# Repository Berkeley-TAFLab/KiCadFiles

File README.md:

# KiCadFiles
Attempting version control on KiCadFiles. Hopefully this works.

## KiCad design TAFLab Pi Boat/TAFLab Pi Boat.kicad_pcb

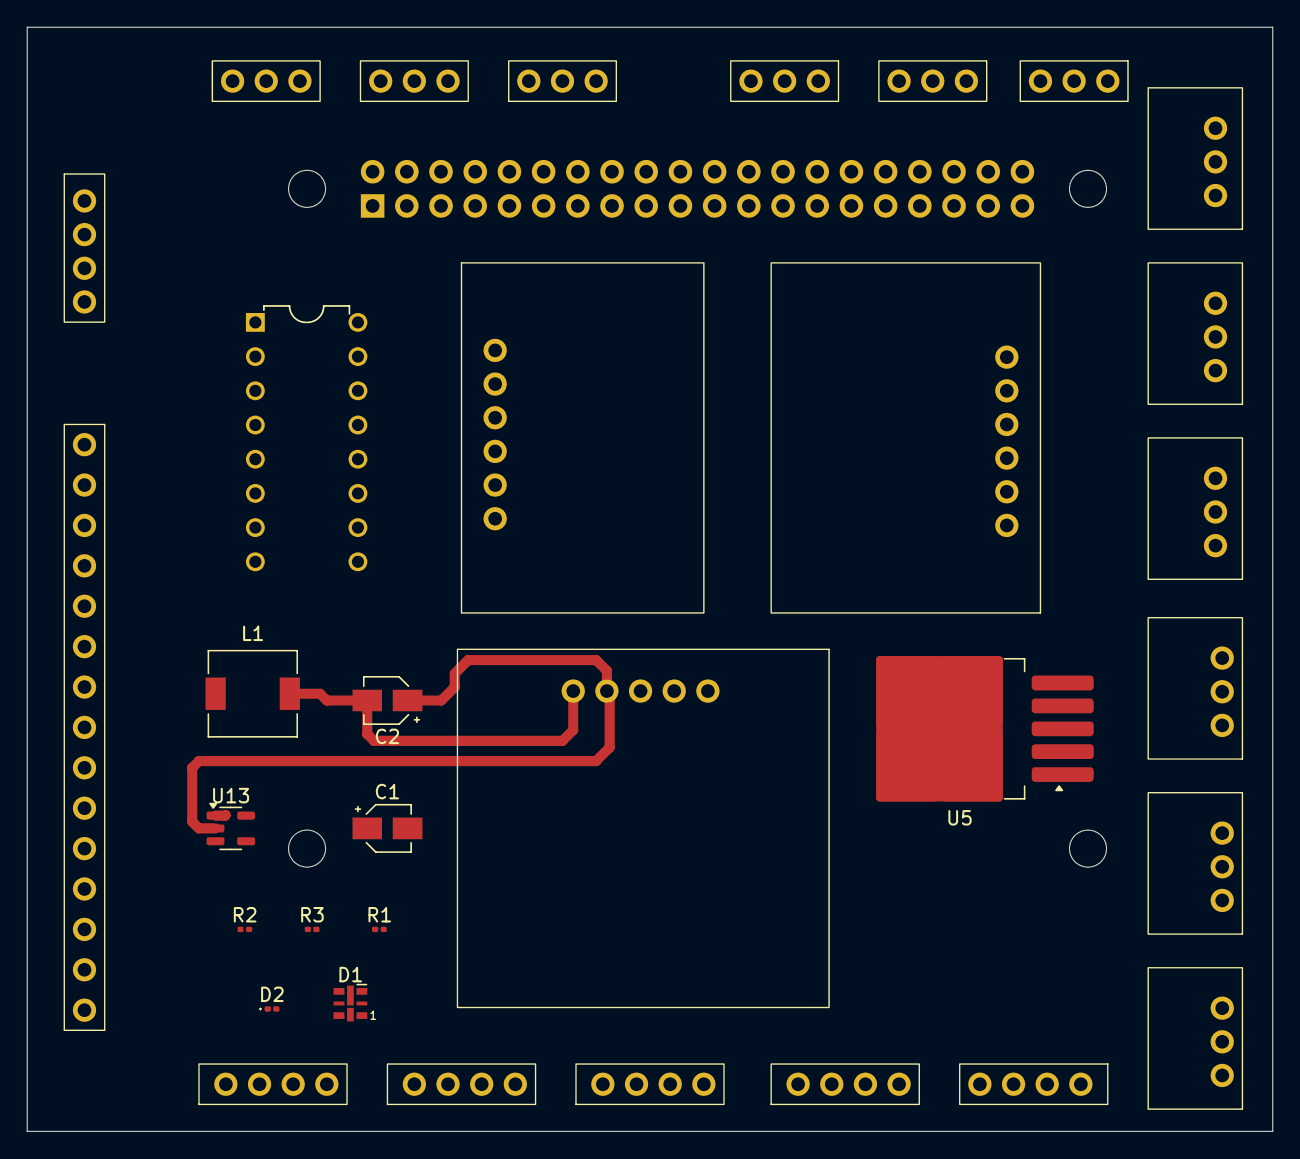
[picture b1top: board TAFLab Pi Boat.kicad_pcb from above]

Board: 2 copper layers, 92.5 x 82.0 mm, 34 parts (0 on the bottom side), 33 nets.

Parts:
C1: 680 uF; CP_Elec_3x5.3
C2: 220 uF; CP_Elec_3x5.3
D1: LED; LED-APA102-2020
D2: D; D_0201_0603Metric
L1: 33uH; L_6.3x6.3_H3
R1: 300Ω; R_0201_0603Metric
R2: 160Ω; R_0201_0603Metric
R3: 10Ω; R_0201_0603Metric
RP1: Raspberry_Pi_2_3; RaspberryPi_4
U4: GT-U7_GPS
U5: LM2596S-5; TO-263-5_TabPin3
U6: MPU6050_IMU_Accelerometer
U7, U8, U9: DS18B20_Water_Temp_Sensor
U10, U11, U12: HW038_WaterLevelSensor
U13: AD8603; TSOT-23-5
U14, U25, U26, U27, U28, U29: Default4Pin
U15: INA219_BatteryPowerSensor
U19, U20, U21, U22, U23, U24: Default3Pin
U33: MCP3008
U34: RearWireConnector

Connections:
+3.3V: RP1.1 (+3.3V_1), U33.15 (Vref), U33.16 (Vdd)
+5V: C2.2, L1.2, R1.1, RP1.2 (+5V_1), U4.5 (5V), U5.4 (FB), U6.1 (5V), U7.2 (5V), U8.2 (5V), U9.2 (5V), U10.2 (5V), U11.2 (5V), U12.2 (5V), U13.3 (+), U14.1 (5V), U15.1 (5V), U19.1 (5V), U20.1 (5V), U21.1 (5V), U22.1 (5V), U23.1 (5V), U24.1 (5V), U25.1 (5V), U26.1 (5V), U27.1 (5V), U28.1 (5V), U29.1 (5V), U34.1 (5V), U34.4 (5V)
+8V: R2.2, U13.1, U34.7 (8V), U34.12 (8V)
A0: U33.1 (CH0), U34.14 (ANA)
A1: U10.1 (ANA), U33.2 (CH1)
A2: U11.1 (ANA), U33.3 (CH2)
A3: U12.1 (ANA), U33.4 (CH3)
A4: U22.3 (DIG/ANA), U33.5 (CH4)
A5: U23.3 (DIG/ANA), U33.6 (CH5)
A6: U24.3 (DIG/ANA), U33.7 (CH6)
BAT+: C1.2, U5.1 (VIN), U34.10 (BAT+)
BAT-: C1.1, U5.5 (~ON/OFF), U34.11 (BAT-)
CLK: RP1.40 (GPIO21/SPI0_SCLK1), U33.13 (CLK)
CS/SHDN: RP1.11 (GPIO_17/SPI1_CS1), U33.10 (~CS/SHDN)
D0: RP1.7 (GPIO_4/GPCLK0), U7.1 (DIG)
D1: RP1.13 (GPIO27), U8.1 (DIG)
D2: RP1.15 (GPIO_22), U9.1 (DIG)
D3: RP1.16 (GPIO_23), U19.3 (DIG/ANA)
D4: RP1.19 (GPIO_10/SPI0_MOSI), U20.3 (DIG/ANA)
D5: RP1.22 (GPIO_25), U21.3 (DIG/ANA)
DIN: RP1.38 (GPIO20/SPI0_MOSI1), U33.11 (Din)
DOUT: RP1.35 (GPIO19/SPI0_MISO1/PWM1), U33.12 (Dout)
GND: C2.1, D1.1 (K), D2.2 (A), R3.2, RP1.6 (GND_1), U4.4 (GND), U5.3 (GND), U6.3 (GND), U7.3 (GND), U8.3 (GND), U9.3 (GND), U10.3 (GND), U11.3 (GND), U12.3 (GND), U13.2 (V-), U14.2 (GND), U15.2 (GND), U19.2 (GND), U20.2 (GND), U21.2 (GND), U22.2 (GND), U23.2 (GND), U24.2 (GND), U25.2 (GND), U26.2 (GND), U27.2 (GND), U28.2 (GND), U29.2 (GND), U33.9 (DGND), U33.14 (AGND), U34.2 (GND), U34.5 (GND), U34.8 (GND), U34.13 (GND)
unnamed: D1.2 (A), R1.2
unnamed: D2.1 (K), L1.1, U5.2 (OUT)
unnamed: R2.1, R3.1, U13.4 (-)
PWM0: RP1.32 (GPIO12/PWM0), U34.9 (DIG)
PWM1: RP1.33 (GPIO13/PWM1), U34.6 (DIG)
PWM2: RP1.12 (GPIO_18/PWM0/SPI1_CS0), U34.3 (DIG)
RX0: RP1.8 (GPIO_14/[UART]_TXD0), U4.3 (RX)
SCL: RP1.5 (GPIO_3/[I2C]_SCL), U6.4 (SCL), U14.4 (SCL), U15.3 (SCL), U25.4 (SCL), U26.4 (SCL), U27.4 (SCL), U28.4 (SCL), U29.4 (SCL)
SDA: RP1.3 (GPIO_2/[I2C]_SDA), U6.5 (SDA), U14.3 (SDA), U15.4 (SDA), U25.3 (SDA), U26.3 (SDA), U27.3 (SDA), U28.3 (SDA), U29.3 (SDA)
TX0: RP1.10 (GPIO_15/[UART]_RXD0), U4.2 (TX)

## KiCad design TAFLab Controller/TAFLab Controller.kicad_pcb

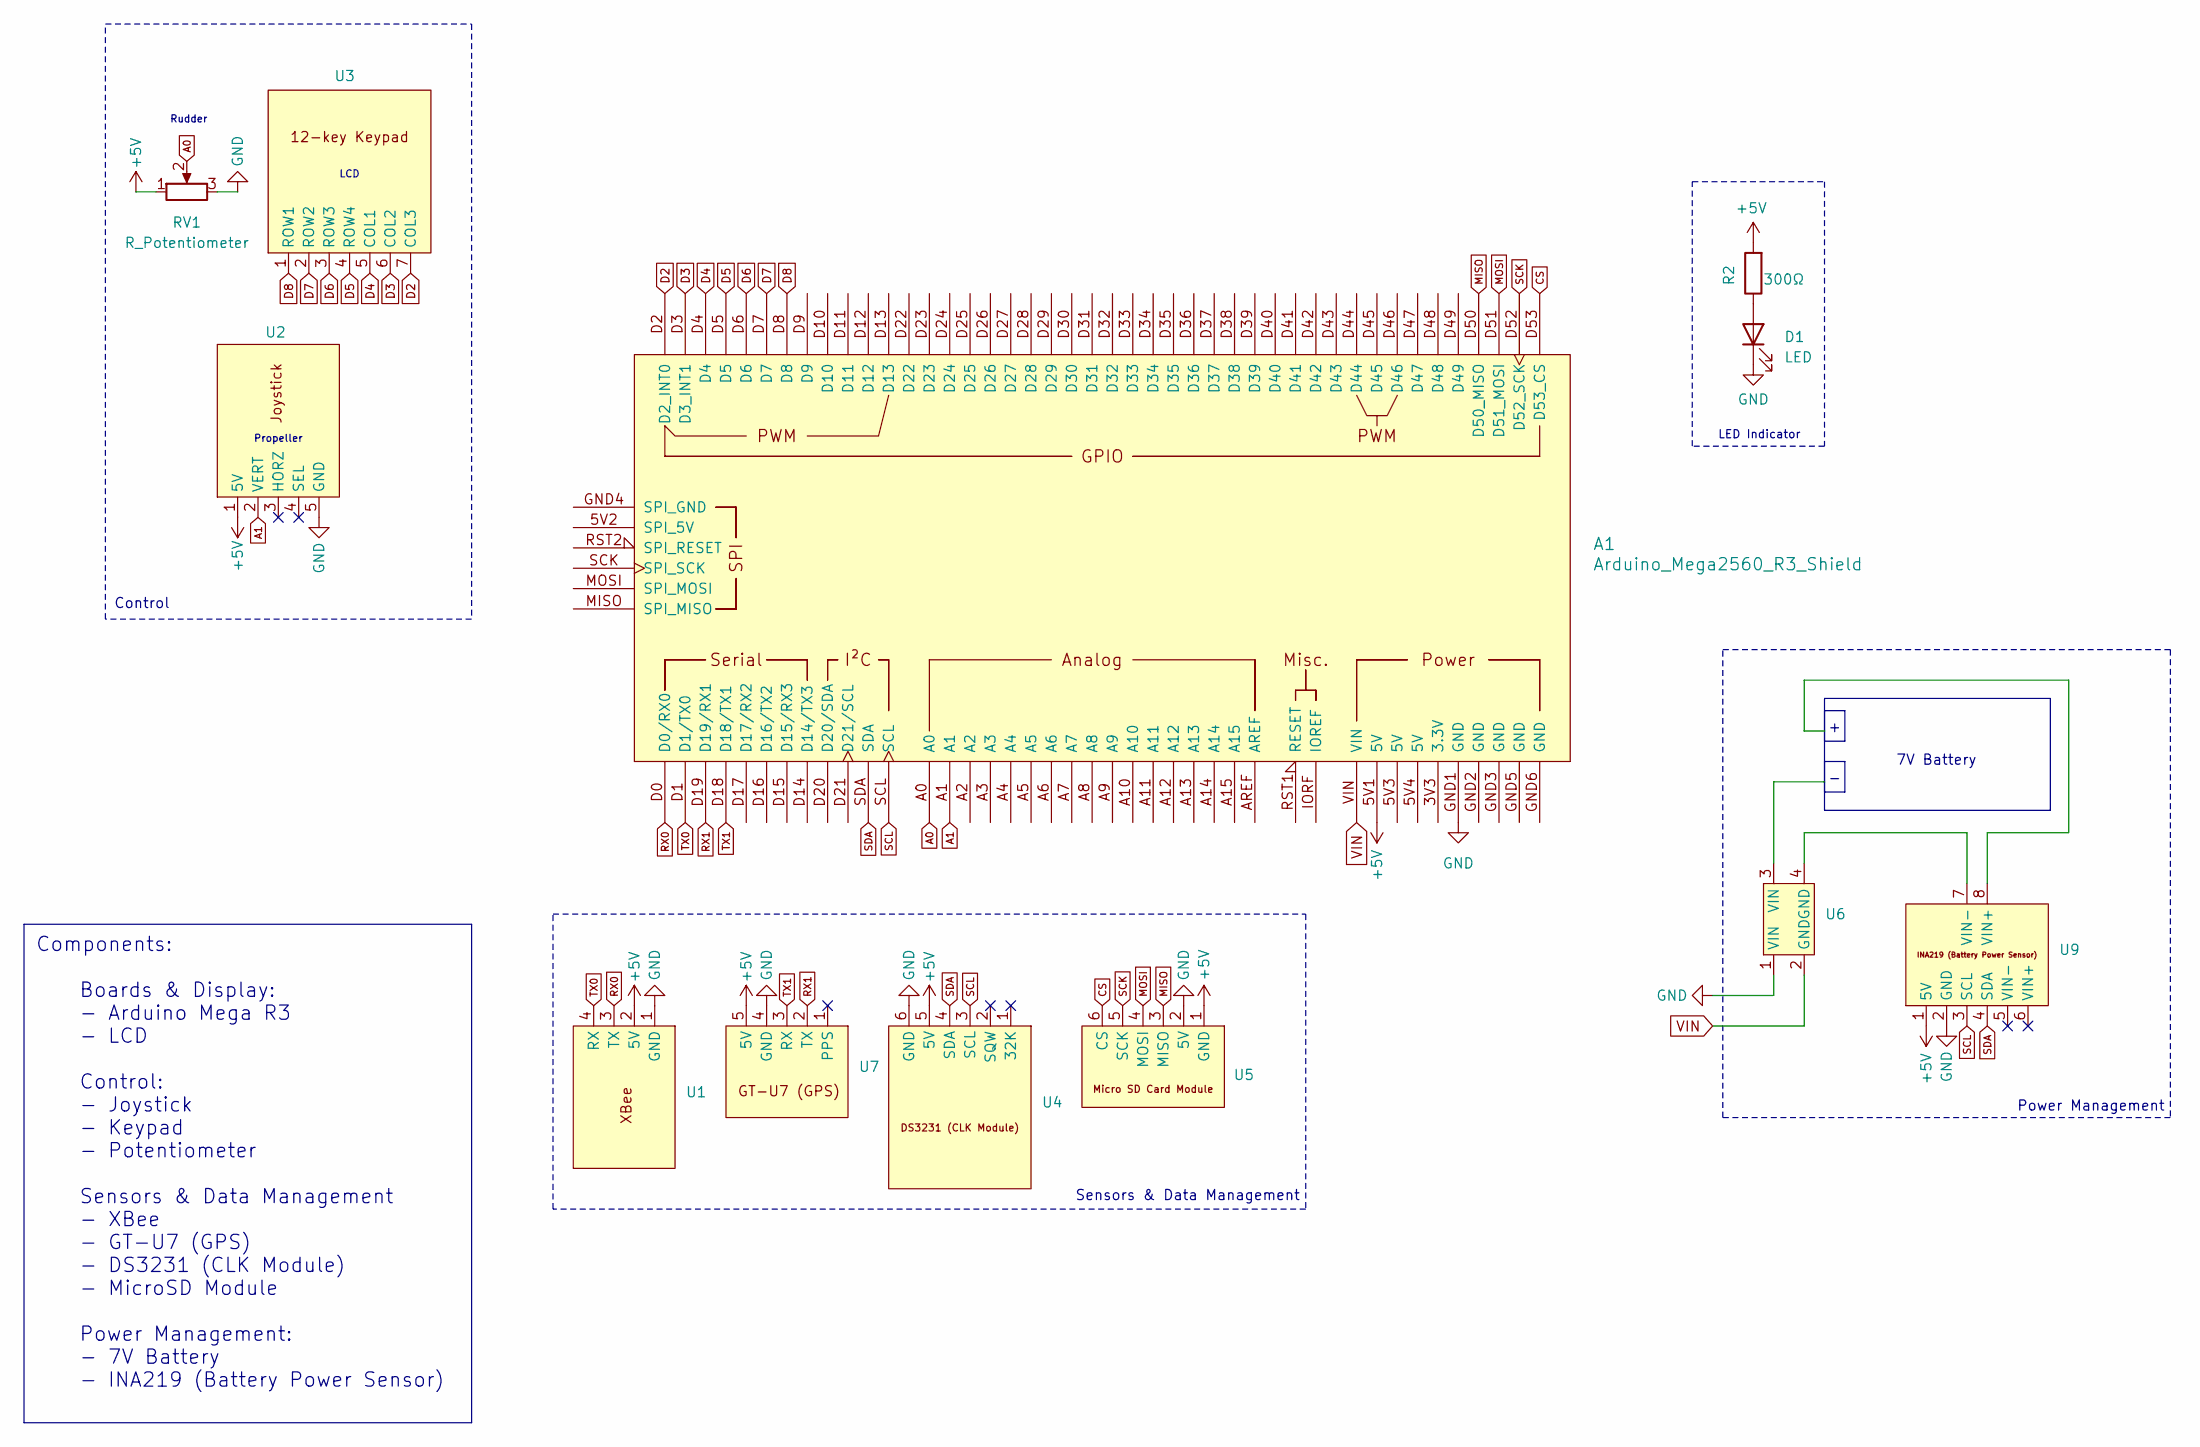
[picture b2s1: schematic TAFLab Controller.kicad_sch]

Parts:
A1: Arduino_Mega2560_R3_Shield
D1: LED; Default2Pin
R2: 300Ω; Default2Pin
RV1: R_Potentiometer; Potentiometer
U1: XBeeBreakout
U2: JoyStick
U3: Keypad
U4: HW84_DS3231_CLK_Module
U5: Micro_SD_Module
U6: VinArduinoConnector
U7: GT-U7_GPS
U9: INA219_BatteryPowerSensor

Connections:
+5V: A1.5V1 (5V), R2.2, RV1.1, U1.2 (5V), U2.1 (5V), U4.5 (5V), U5.1 (GND), U7.5 (5V), U9.1 (5V)
A0: A1.A0, RV1.2
A1: A1.A1, U2.2 (VERT)
CS: A1.D53 (D53_CS), U5.6 (CS)
D2: A1.D2 (D2_INT0), U3.7 (COL3)
D3: A1.D3 (D3_INT1), U3.6 (COL2)
D4: A1.D4, U3.5 (COL1)
D5: A1.D5, U3.4 (ROW4)
D6: A1.D6, U3.3 (ROW3)
D7: A1.D7, U3.2 (ROW2)
D8: A1.D8, U3.1 (ROW1)
GND: A1.GND1 (GND), D1.1 (K), RV1.3, U1.1 (GND), U2.5 (GND), U4.6 (GND), U5.2 (5V), U6.1 (VIN), U7.4 (GND), U9.2 (GND)
MISO: A1.D50 (D50_MISO), U5.3 (MISO)
MOSI: A1.D51 (D51_MOSI), U5.4 (MOSI)
unnamed: D1.2 (A), R2.1
RX0: A1.D0 (D0/RX0), U1.3 (TX)
RX1: A1.D19 (D19/RX1), U7.2 (TX)
SCK: A1.D52 (D52_SCK), U5.5 (SCK)
SCL: A1.SCL, U4.3 (SCL), U9.3 (SCL)
SDA: A1.SDA, U4.4 (SDA), U9.4 (SDA)
TX0: A1.D1 (D1/TX0), U1.4 (RX)
TX1: A1.D18 (D18/TX1), U7.3 (RX)
VIN: A1.VIN, U6.2 (GND)

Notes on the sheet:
Components: Boards & Display: - Arduino Mega R3 - LCD Control: - Joystick - Keypad - Potentiometer Sensors & Data Management - XBee - GT-U7 (GPS) - DS3231 (CLK Module) - MicroSD Module Power Management: - 7V Battery - INA219 (Battery Power Sensor)
LED Indicator
7V Battery
Propeller
Power Management
Sensors & Data Management
Rudder
LCD
Control

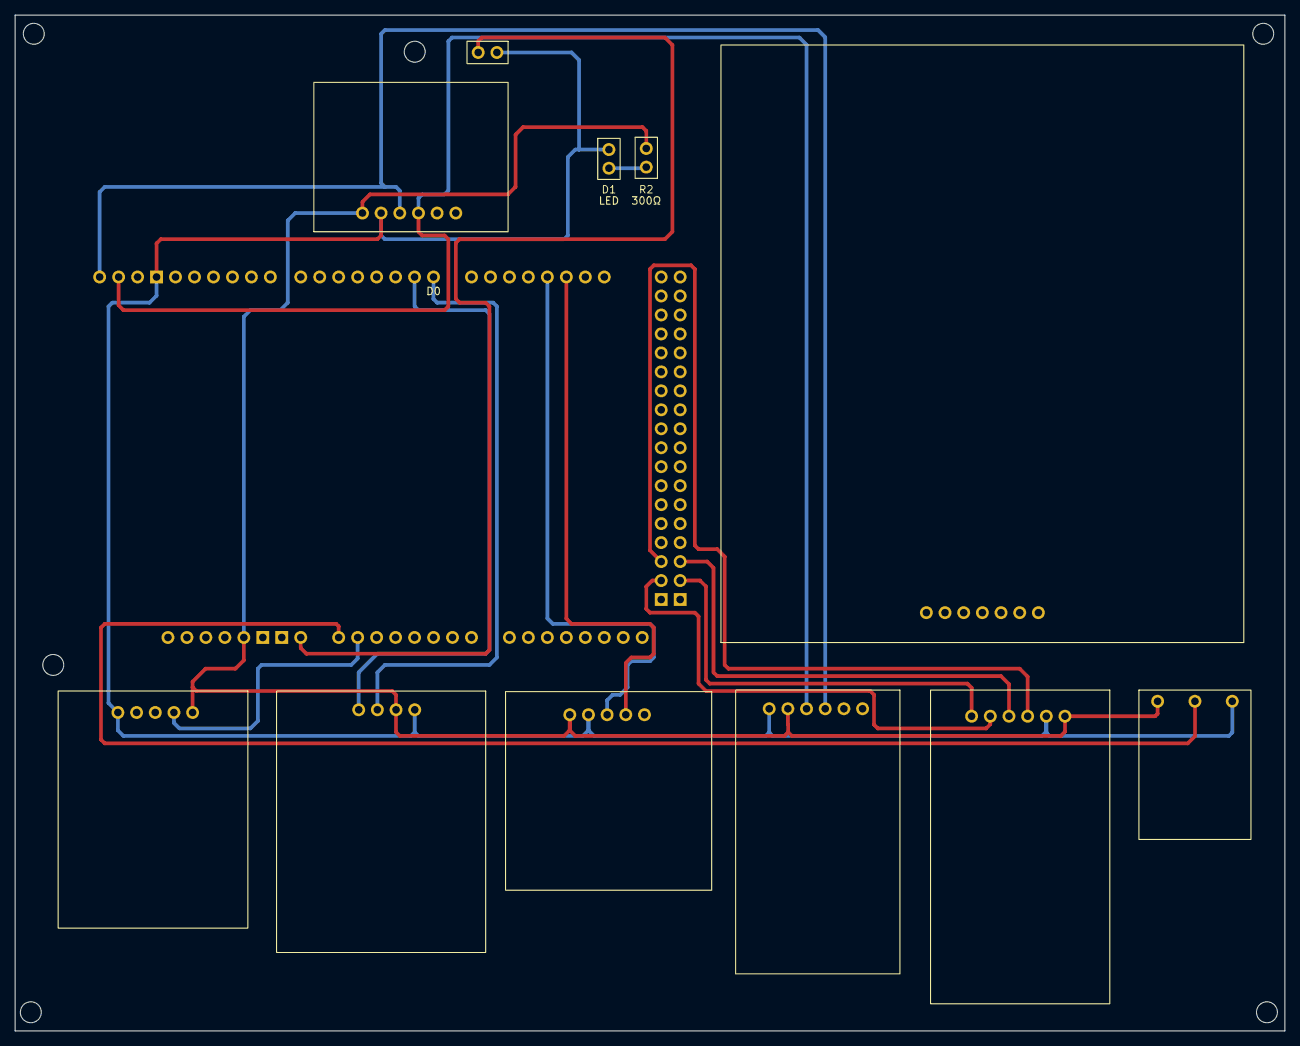
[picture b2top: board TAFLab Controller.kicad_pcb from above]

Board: 4 copper layers, 170.0 x 136.0 mm, 12 parts (0 on the bottom side), 23 nets.

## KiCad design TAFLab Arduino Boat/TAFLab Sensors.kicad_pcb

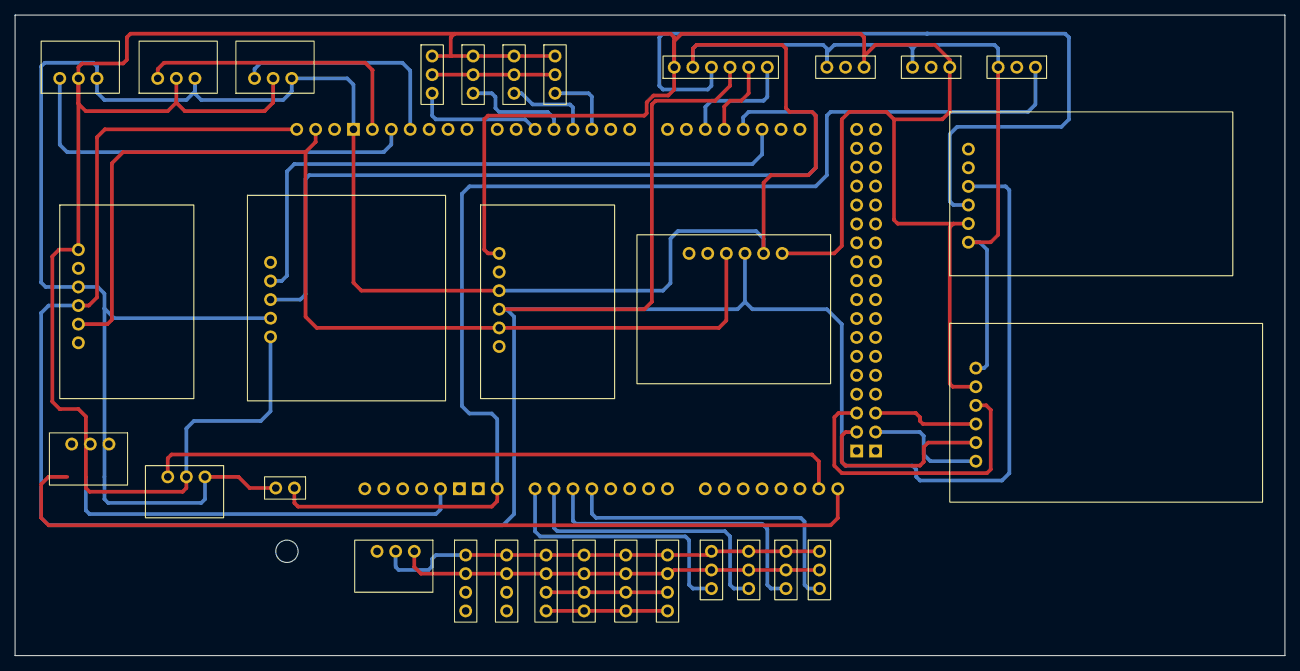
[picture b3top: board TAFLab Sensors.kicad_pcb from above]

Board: 4 copper layers, 170.5 x 86.0 mm, 32 parts (0 on the bottom side), 34 nets.

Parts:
A1: Arduino_Mega2560_R3_Shield
U2: LIS3MDL_Magnetometer
U3: MPU6050_IMU_Accelerometer
U4: INA219_BatteryPowerSensor
U7: GT-U7_GPS
U9, U21, U36: HW038_WaterLevelSensor
U10, U19, U20: DS18B20_Water_Temp_Sensor
U11: Micro_SD_Module
U13: HW84_DS3231_CLK_Module
U14, U16, U17: ActuatorConnector
U15, U23, U24, U25, U27, U28, U29, U30: Default3Pin
U18: SailWireConnector
U22: VinArduinoConnector
U26, U31, U32, U33, U34, U35: Default4Pin

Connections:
5V: A1.5V1 (5V), U2.1 (5V), U3.1 (5V), U4.1 (5V), U7.5 (5V), U9.2 (5V), U10.2 (5V), U11.2 (5V), U13.5 (5V), U14.1 (5V), U15.1 (5V), U17.1 (5V), U18.1 (5V), U19.2 (5V), U20.2 (5V), U21.2 (5V), U23.1 (5V), U24.1 (5V), U25.1 (5V), U26.1 (5V), U27.1 (5V), U28.1 (5V), U29.1 (5V), U30.1 (5V), U31.1 (5V), U32.1 (5V), U33.1 (5V), U34.1 (5V), U35.1 (5V), U36.2 (5V)
8V: A1.VIN, U16.1 (8V), U22.1 (VIN)
A0: A1.A0, U25.3 (DIG/ANA)
A1: A1.A1, U24.3 (DIG/ANA)
A2: A1.A2, U23.3 (DIG/ANA)
A3: A1.A3, U15.3 (DIG/ANA)
A13: A1.A13, U36.1 (ANA)
A14: A1.A14, U21.1 (ANA)
A15: A1.A15, U9.1 (ANA)
CS: A1.D53 (D53_CS), U11.6 (CS)
D2: A1.D2 (D2_INT0), U30.3 (DIG/ANA)
D3: A1.D3 (D3_INT1), U29.3 (DIG/ANA)
D4: A1.D4, U28.3 (DIG/ANA)
D5: A1.D5, U27.3 (DIG/ANA)
D8: A1.D8, U16.2 (DIG)
D9: A1.D9, U17.2 (DIG)
D10: A1.D10, U14.2 (DIG)
D11: A1.D11, U19.1 (DIG)
D12: A1.D12, U10.1 (DIG)
D13: A1.D13, U20.1 (DIG)
GND: A1.GND1 (GND), U2.3 (GND), U3.3 (GND), U4.2 (GND), U7.4 (GND), U9.3 (GND), U10.3 (GND), U11.1 (GND), U13.6 (GND), U14.3 (GND), U15.2 (GND), U16.3 (GND), U17.3 (GND), U18.2 (GND), U19.3 (GND), U20.3 (GND), U21.3 (GND), U22.2 (GND), U23.2 (GND), U24.2 (GND), U25.2 (GND), U26.2 (GND), U27.2 (GND), U28.2 (GND), U29.2 (GND), U30.2 (GND), U31.2 (GND), U32.2 (GND), U33.2 (GND), U34.2 (GND), U35.2 (GND), U36.3 (GND)
MISO: A1.D50 (D50_MISO), U11.3 (MISO)
MOSI: A1.D51 (D51_MOSI), U11.4 (MOSI)
RX0: A1.D1 (D1/TX0), U31.3 (RX)
RX1: A1.D18 (D18/TX1), U7.3 (RX)
RX2: A1.D16 (D16/TX2), U18.6 (RX)
RX3: A1.D14 (D14/TX3), U26.3 (RX)
SCK: A1.D52 (D52_SCK), U11.5 (SCK)
SCL: A1.SCL, U2.4 (SCL), U3.4 (SCL), U4.3 (SCL), U13.3 (SCL), U18.4 (SCL), U32.4 (SCL), U33.4 (SCL), U34.4 (SCL), U35.4 (SCL)
SDA: A1.SDA, U2.5 (SDA), U3.5 (SDA), U4.4 (SDA), U13.4 (SDA), U18.3 (SDA), U32.3 (SDA), U33.3 (SDA), U34.3 (SDA), U35.3 (SDA)
TX0: A1.D0 (D0/RX0), U31.4 (TX)
TX1: A1.D19 (D19/RX1), U7.2 (TX)
TX2: A1.D17 (D17/RX2), U18.5 (TX)
TX3: A1.D15 (D15/RX3), U26.4 (TX)

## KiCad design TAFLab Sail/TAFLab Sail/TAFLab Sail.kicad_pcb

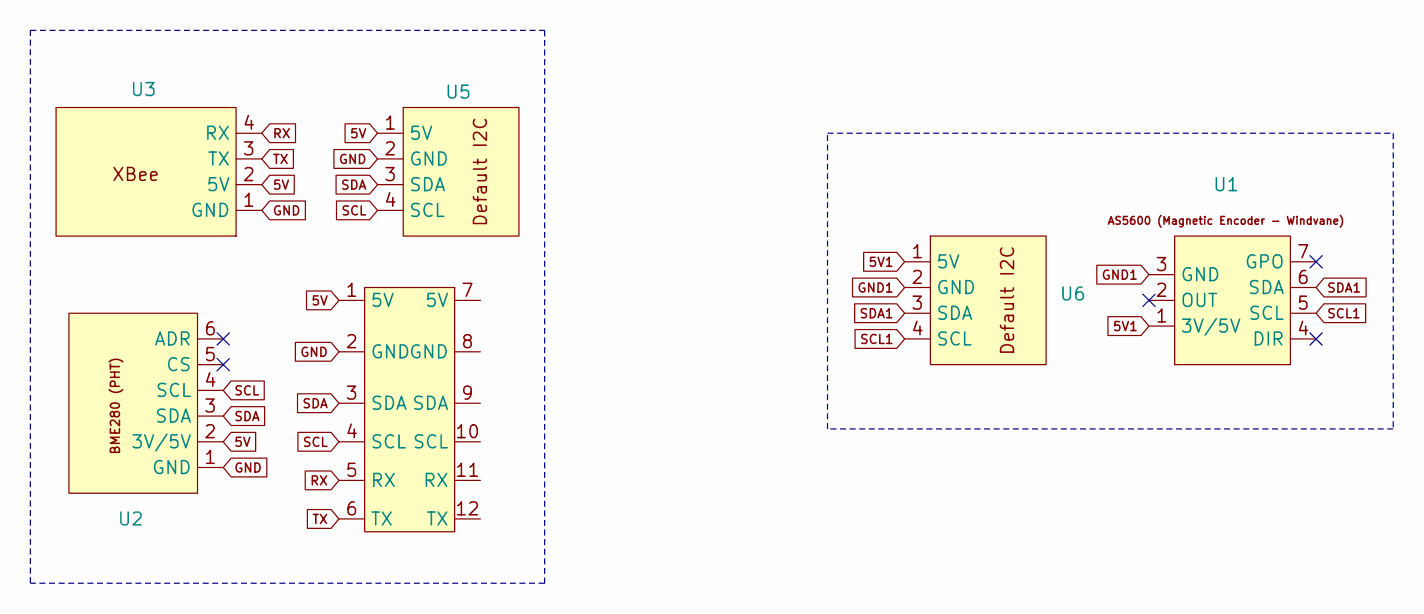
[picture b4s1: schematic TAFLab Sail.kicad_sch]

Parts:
U1: AS5600_Magnetic_Encoder_Windvane
U2: BME280_PHT
U3: XBeeBreakout
U4: Top_Boat_PCB
U5, U6: Default4Pin

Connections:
5V: U2.2 (3V/5V), U3.2 (5V), U4.1 (5V), U5.1 (5V)
5V1: U1.1 (3V/5V), U6.1 (5V)
GND: U2.1 (GND), U3.1 (GND), U4.2 (GND), U5.2 (GND)
GND1: U1.3 (GND), U6.2 (GND)
RX: U3.4 (RX), U4.5 (RX)
SCL: U2.4 (SCL), U4.4 (SCL), U5.4 (SCL)
SCL1: U1.5 (SCL), U6.4 (SCL)
SDA: U2.3 (SDA), U4.3 (SDA), U5.3 (SDA)
SDA1: U1.6 (SDA), U6.3 (SDA)
TX: U3.3 (TX), U4.6 (TX)

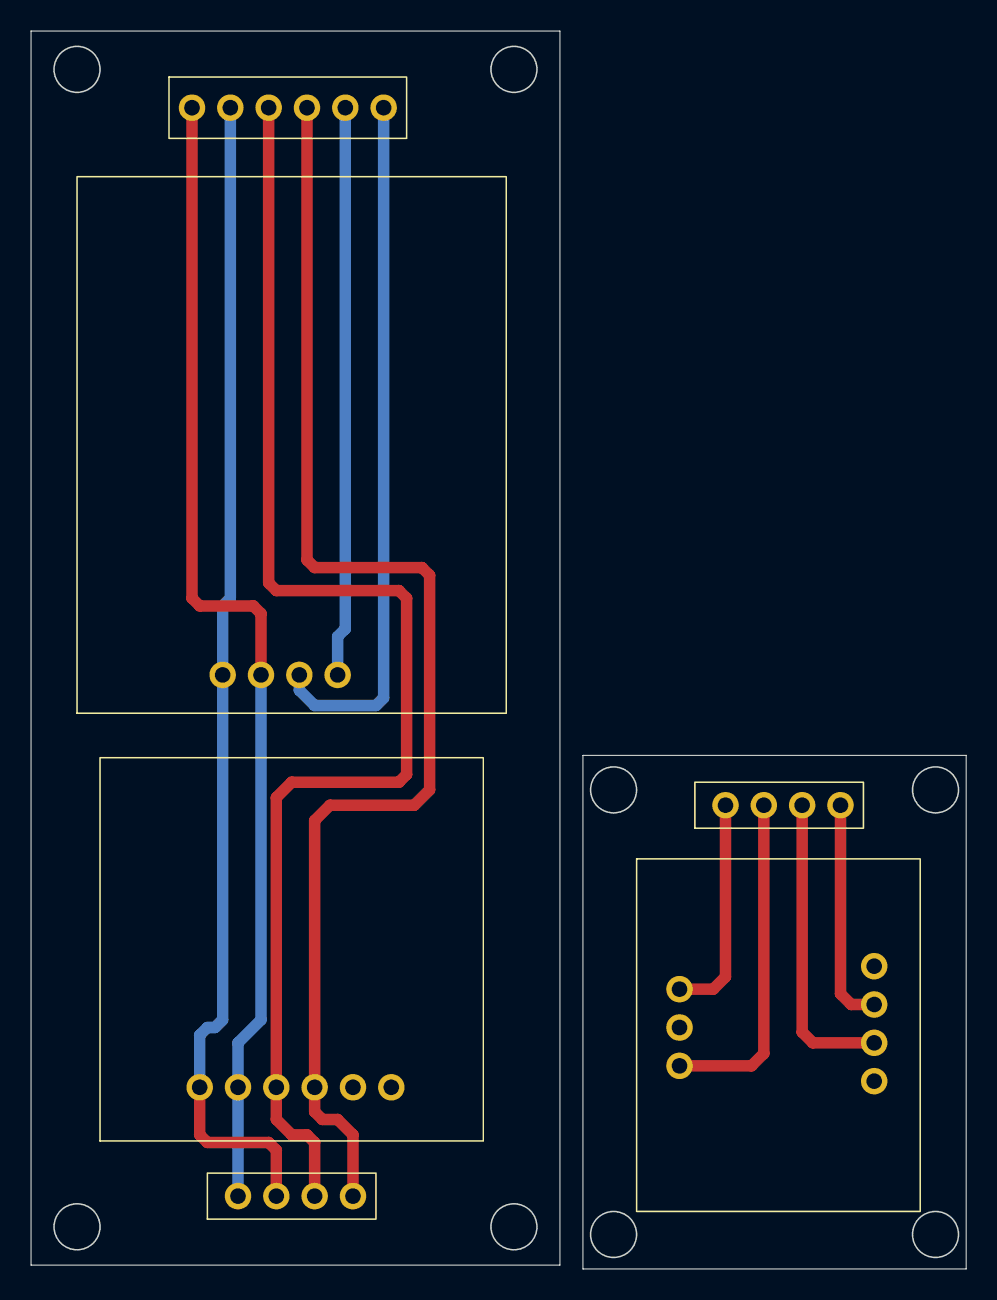
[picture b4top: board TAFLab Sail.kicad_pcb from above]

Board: 2 copper layers, 61.0 x 80.8 mm, 6 parts (0 on the bottom side), 10 nets.

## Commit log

2024-10-31 Add basic ESP Boat Schematic. Hope it works
2024-11-02 First commit. We'll see if this works
2024-11-02 Update schematic
2025-02-20 Added PCB files
